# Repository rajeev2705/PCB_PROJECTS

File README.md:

# PCB_PROJECTS
Welcome to my PCB projects repository! This space is dedicated to documenting my journey in designing, creating, and improving printed circuit boards (PCBs). Here, I share various PCB projects, including schematics, layouts, bill of materials (BOM), and relevant documentation.

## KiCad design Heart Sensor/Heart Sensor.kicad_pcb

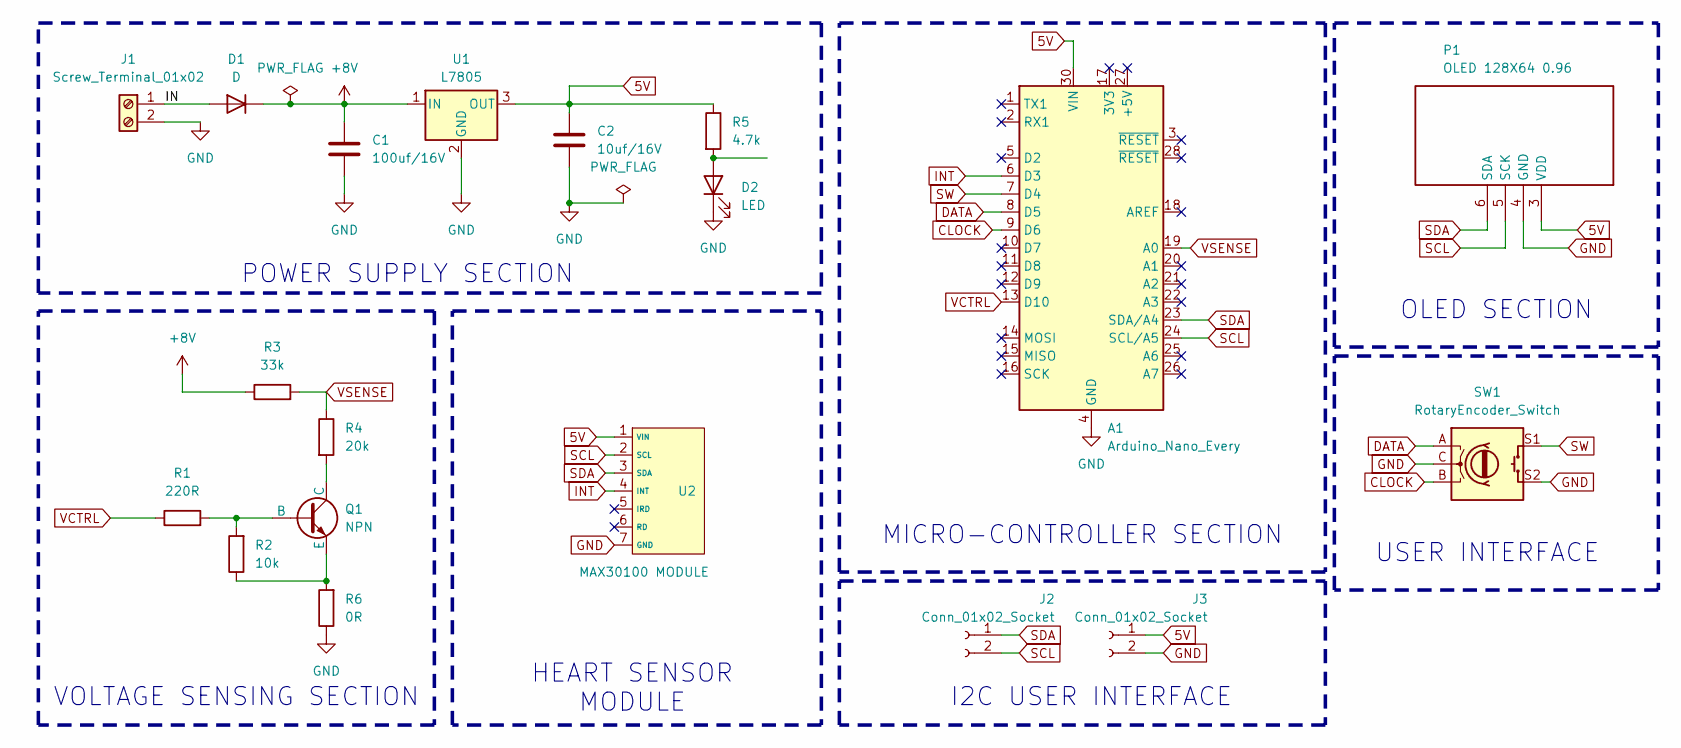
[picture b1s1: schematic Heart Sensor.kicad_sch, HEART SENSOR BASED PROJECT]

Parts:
A1: Arduino_Nano_Every; Arduino_Nano
C1: 100uf/16V; C_Radial_D5.0mm_H5.0mm_P2.00mm
C2: 10uf/16V; C_Radial_D5.0mm_H5.0mm_P2.00mm
D1: D; D_A-405_P7.62mm_Horizontal
D2: LED; LED_D3.0mm
J1: Screw_Terminal_01x02; TerminalBlock_4Ucon_1x02_P3.50mm_Horizontal_user
J2, J3: Conn_01x02_Socket; PinSocket_1x02_P2.54mm_Vertical
P1: OLED 128X64 0.96; OLED_MODULE _FOOTPRINT
Q1: NPN; TO-92L_Inline
R1: 220R; R_Axial_DIN0207_L6.3mm_D2.5mm_P10.16mm_Horizontal
R2: 10k; R_Axial_DIN0207_L6.3mm_D2.5mm_P10.16mm_Horizontal
R3: 33k; R_Axial_DIN0207_L6.3mm_D2.5mm_P10.16mm_Horizontal
R4: 20k; R_Axial_DIN0207_L6.3mm_D2.5mm_P10.16mm_Horizontal
R5: 4.7k; R_Axial_DIN0207_L6.3mm_D2.5mm_P10.16mm_Horizontal
R6: 0R; R_Axial_DIN0207_L6.3mm_D2.5mm_P10.16mm_Horizontal
SW1: RotaryEncoder_Switch; rotary_ncodeer
U1: L7805; TO-220-3_Vertical
U2: MAX30100 MODULE; MAX30100_MODULE

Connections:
5V: A1.30 (VIN), C2.1, J3.1, P1.3 (VDD), R5.1, U1.3 (OUT), U2.1 (VIN)
+8V: C1.1, D1.1 (K), R3.1, U1.1 (IN)
/IN: D1.2 (A), J1.1
CLOCK: A1.9 (D6), SW1.B
DATA: A1.8 (D5), SW1.A
GND: A1.4 (GND), A1.29 (GND), C1.2, C2.2, D2.1 (K), J1.2, J3.2, P1.4 (GND), R6.1, SW1.C, SW1.S2, U1.2 (GND), U2.7 (GND)
INT: A1.6 (D3), U2.4 (INT)
unnamed: D2.2 (A), R5.2
unnamed: Q1.2 (B), R1.2, R2.2
unnamed: Q1.1 (C), R4.2
unnamed: Q1.3 (E), R2.1, R6.2
SCL: A1.24 (SCL/A5), J2.2, P1.5 (SCK), U2.2 (SCL)
SDA: A1.23 (SDA/A4), J2.1, P1.6 (SDA), U2.3 (SDA)
SW: A1.7 (D4), SW1.S1
VCTRL: A1.13 (D10), R1.1
VSENSE: A1.19 (A0), R3.2, R4.1

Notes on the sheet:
HEART SENSOR MODULE
USER INTERFACE
I2C USER INTERFACE
POWER SUPPLY SECTION
VOLTAGE SENSING SECTION
OLED SECTION
MICRO-CONTROLLER SECTION

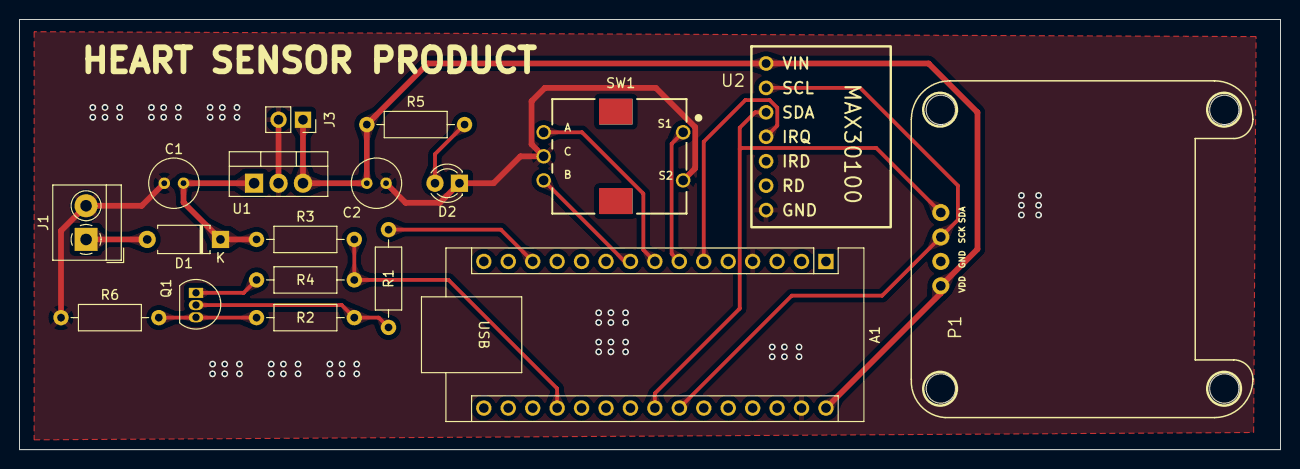
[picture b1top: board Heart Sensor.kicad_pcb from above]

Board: 2 copper layers, 131.1 x 44.7 mm, 18 parts (0 on the bottom side), 16 nets.

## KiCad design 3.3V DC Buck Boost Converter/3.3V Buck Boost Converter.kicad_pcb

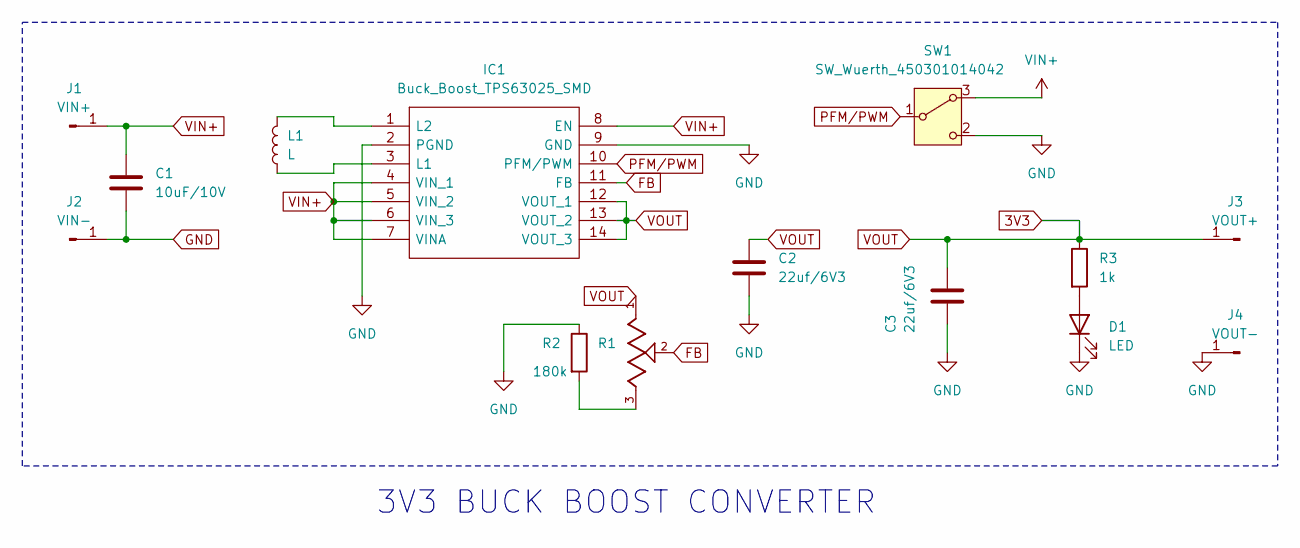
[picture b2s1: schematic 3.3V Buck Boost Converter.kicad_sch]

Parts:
C1: 10uF/10V; C_Radial_D6.3mm_H11.0mm_P2.50mm
C2, C3: 22uf/6V3; C_Radial_D6.3mm_H11.0mm_P2.50mm
D1: LED; LED_D3.0mm
IC1: Buck_Boost_TPS63025_SMD; IC_BuckBoost_TPS630250RNCT_VQFN14_2x3mm; Manufacturer_Part_Number TPS630250RNCT; Mouser Part Number 595-TPS630250RNCT
J1: VIN+; TestPoint_Pad_1.0x1.0mm
J2: VIN-; TestPoint_Pad_1.0x1.0mm
J3: VOUT+; TestPoint_Pad_1.0x1.0mm
J4: VOUT-; TestPoint_Pad_1.0x1.0mm
L1: L; XFL7015102MEB
R1: PT01-D120K1-B103; TrimPot_10k_SMD; PARTREV 1.0; DigiKey_Part_Number 2223-PT01-D120K1-B103-ND
R2: 180k; R_Axial_DIN0207_L6.3mm_D2.5mm_P10.16mm_Horizontal
R3: 1k; R_Axial_DIN0207_L6.3mm_D2.5mm_P10.16mm_Horizontal
SW1: SW_Wuerth_450301014042; SW_Slide-03_Wuerth-WS-SLTV_10x2.5x6.4_P2.54mm

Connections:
3V3: C2.1, C3.1, IC1.12 (VOUT_1), IC1.13 (VOUT_2), IC1.14 (VOUT_3), J3.1, R1.1, R3.1
FB: IC1.11 (FB), R1.2
GND: C1.2, C2.2, C3.2, D1.1 (K), IC1.2 (PGND), IC1.9 (GND), J2.1, J4.1, R2.1, SW1.2 (C)
unnamed: D1.2 (A), R3.2
unnamed: IC1.3 (L1), L1.1
unnamed: IC1.1 (L2), L1.2
unnamed: R1.3, R2.2
PFM/PWM: IC1.10 (PFM/PWM), SW1.1 (B)
VIN+: C1.1, IC1.4 (VIN_1), IC1.5 (VIN_2), IC1.6 (VIN_3), IC1.7 (VINA), IC1.8 (EN), J1.1, SW1.3 (A)

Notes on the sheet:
3V3 BUCK BOOST CONVERTER

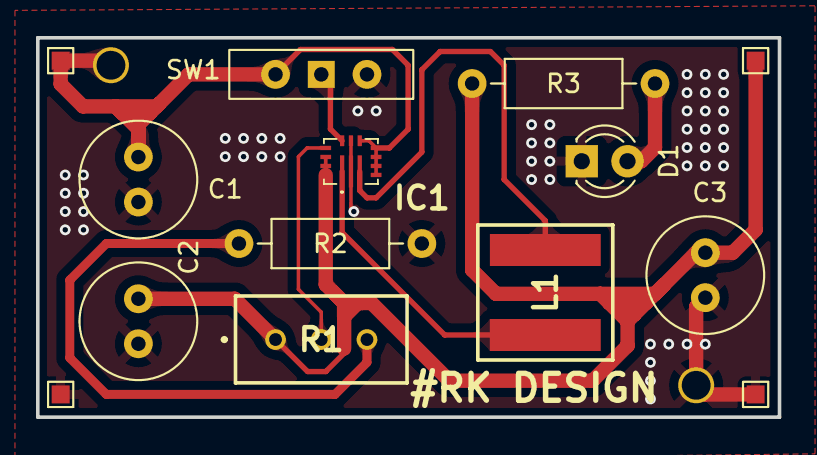
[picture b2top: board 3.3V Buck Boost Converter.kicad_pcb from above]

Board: 2 copper layers, 41.2 x 21.1 mm, 14 parts (0 on the bottom side), 9 nets.

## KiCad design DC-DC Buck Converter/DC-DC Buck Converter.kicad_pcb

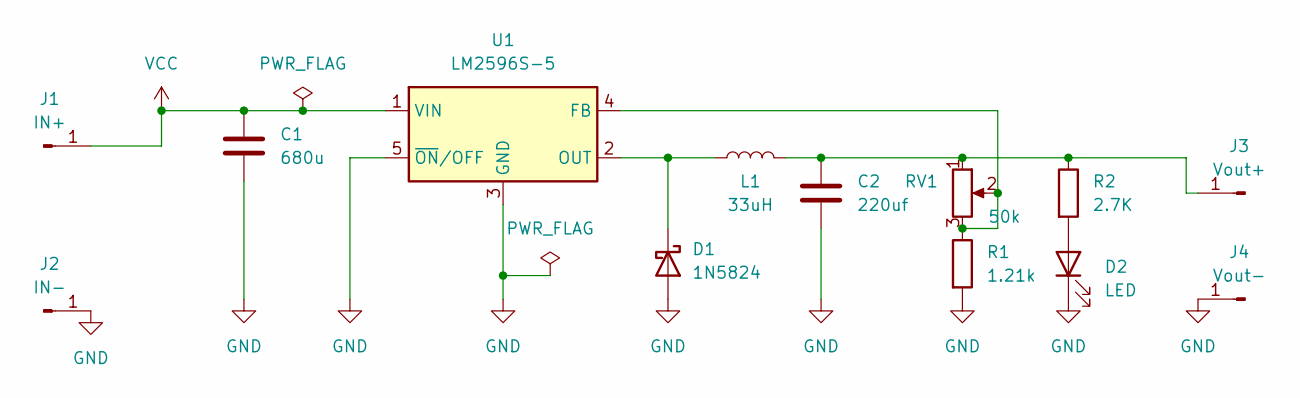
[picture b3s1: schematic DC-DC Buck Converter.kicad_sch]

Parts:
C1: 680u; CAP-SMD_BD6.3-L6.6-W6.6-FD
C2: 220uf; CAP-SMD_BD6.3-L6.6-W6.6-FD
D1: 1N5824; SCHOTTKYDIODE_SMD
D2: LED; LED_0603_1608Metric_Pad1.05x0.95mm_HandSolder
J1: IN+; SolderWire-0.1sqmm_1x01_D0.4mm_OD1mm
J2: IN-; SolderWire-0.1sqmm_1x01_D0.4mm_OD1mm
J3: Vout+; SolderWire-0.1sqmm_1x01_D0.4mm_OD1mm
J4: Vout-; SolderWire-0.1sqmm_1x01_D0.4mm_OD1mm
L1: 33uH; IND_SRP6540-1R0M
R1: 1.21k; R_0603_1608Metric_Pad0.98x0.95mm_HandSolder
R2: 2.7K; R_0603_1608Metric_Pad0.98x0.95mm_HandSolder
RV1: 50k; TrimPot_10k_SMD
U1: LM2596S-5; TO-263-5_TabPin3

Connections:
GND: C1.2, C2.2, D1.2 (A), D2.1 (K), J2.1, J4.1, R1.2, U1.3 (GND), U1.5 (~ON/OFF)
unnamed: D1.1 (K), L1.1, U1.2 (OUT)
unnamed: D2.2 (A), R2.2
unnamed: C2.1, J3.1, L1.2, R2.1, RV1.1
unnamed: R1.1, RV1.2, RV1.3, U1.4 (FB)
VCC: C1.1, J1.1, U1.1 (VIN)

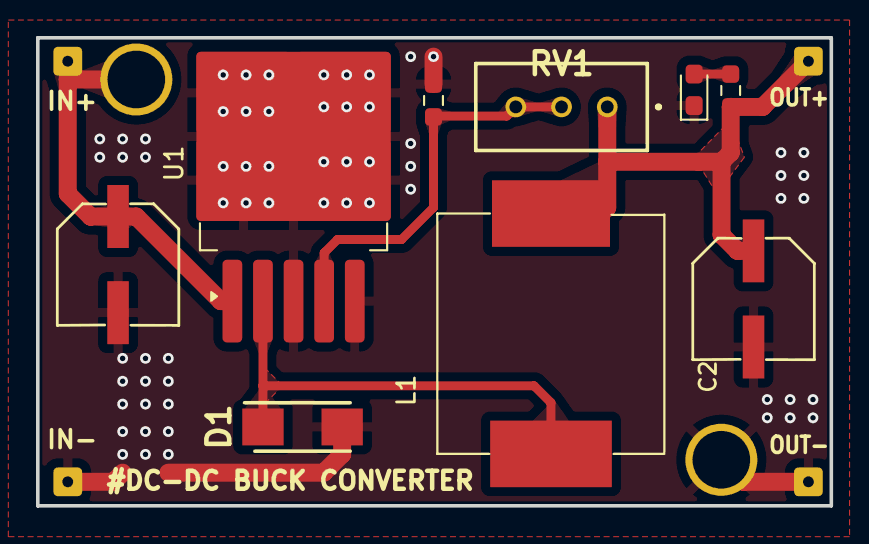
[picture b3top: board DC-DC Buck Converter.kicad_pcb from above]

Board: 2 copper layers, 44.1 x 26.0 mm, 13 parts (0 on the bottom side), 6 nets.

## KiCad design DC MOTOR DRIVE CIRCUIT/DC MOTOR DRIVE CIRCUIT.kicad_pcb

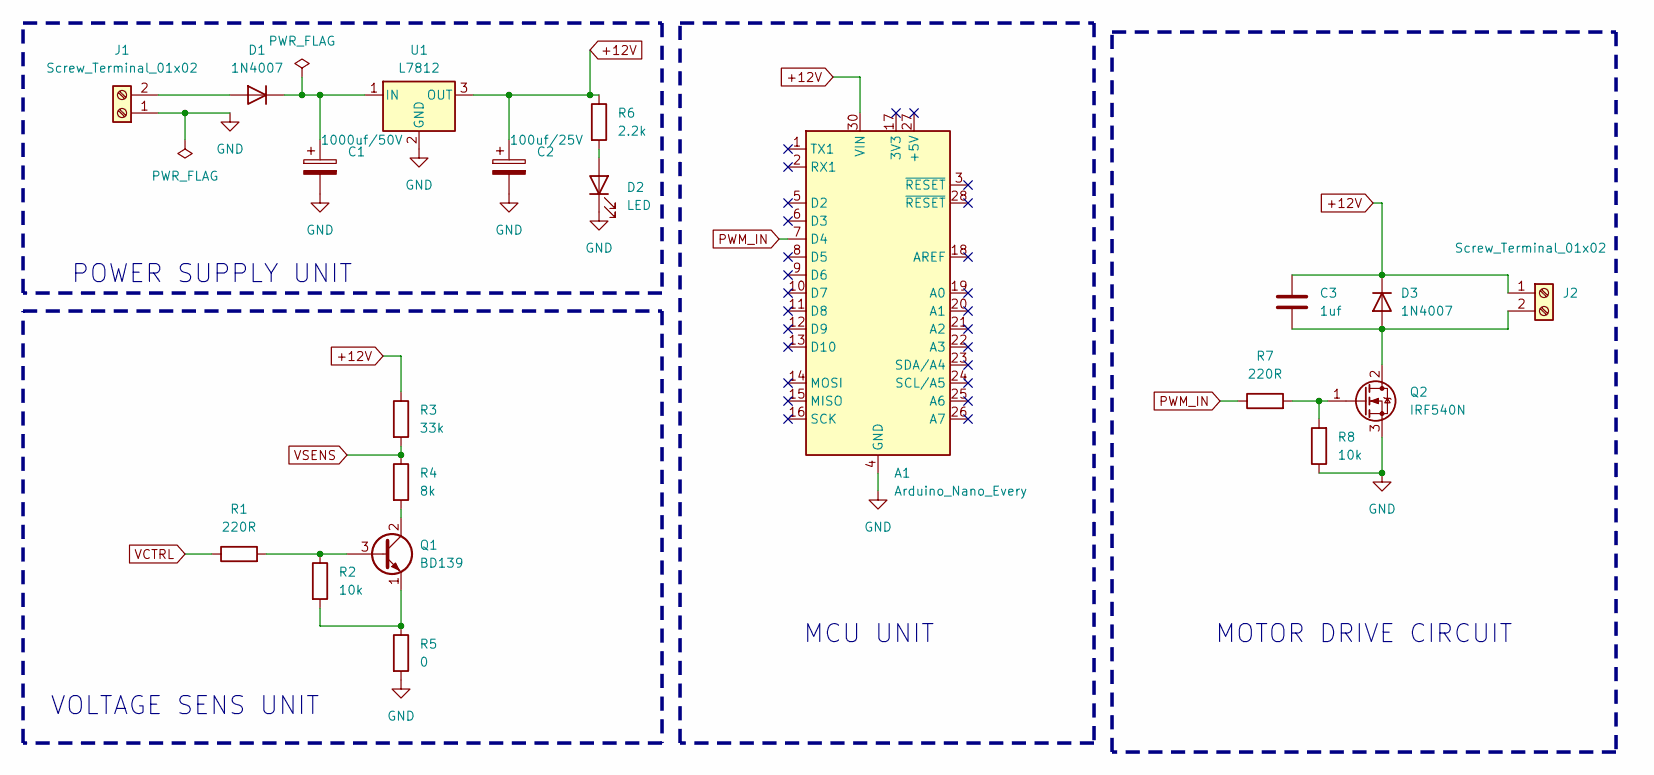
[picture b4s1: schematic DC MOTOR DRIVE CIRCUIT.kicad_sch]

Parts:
A1: Arduino_Nano_Every; Arduino_Nano
C1: 1000uf/50V; CP_Radial_D8.0mm_P3.50mm
C2: 100uf/25V; CP_Radial_D8.0mm_P3.50mm
C3: 1uf; C_Disc_D3.0mm_W1.6mm_P2.50mm
D1, D3: 1N4007; D_DO-41_SOD81_P10.16mm_Horizontal
D2: LED; LED_D3.0mm
J1, J2: Screw_Terminal_01x02; TerminalBlock_4Ucon_1x02_P3.50mm_Horizontal
Q1: BD139; TO-126-3_Vertical
Q2: IRF540N; TO-220-3_Vertical
R1, R7: 220R; R_Axial_DIN0204_L3.6mm_D1.6mm_P7.62mm_Horizontal
R2, R8: 10k; R_Axial_DIN0204_L3.6mm_D1.6mm_P7.62mm_Horizontal
R3: 33k; R_Axial_DIN0204_L3.6mm_D1.6mm_P7.62mm_Horizontal
R4: 8k; R_Axial_DIN0204_L3.6mm_D1.6mm_P7.62mm_Horizontal
R5: 0; R_Axial_DIN0204_L3.6mm_D1.6mm_P7.62mm_Horizontal
R6: 2.2k; R_Axial_DIN0204_L3.6mm_D1.6mm_P7.62mm_Horizontal
U1: L7812; TO-252-2

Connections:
+12V: A1.30 (VIN), C2.1, C3.1, D3.1 (K), J2.1, R3.1, R6.1, U1.3 (OUT)
GND: A1.4 (GND), A1.29 (GND), C1.2, C2.2, D2.1 (K), J1.1, Q2.3 (S), R5.2, R8.1, U1.2 (GND)
unnamed: D1.2 (A), J1.2
unnamed: C1.1, D1.1 (K), U1.1 (IN)
unnamed: D2.2 (A), R6.2
unnamed: C3.2, D3.2 (A), J2.2, Q2.2 (D)
unnamed: Q1.3 (B), R1.2, R2.1
unnamed: Q1.2 (C), R4.2
unnamed: Q1.1 (E), R2.2, R5.1
unnamed: Q2.1 (G), R7.2, R8.2
PWM_IN: A1.7 (D4), R7.1
VCTRL: R1.1
VSENS: R3.2, R4.1

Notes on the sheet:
MOTOR DRIVE CIRCUIT
VOLTAGE SENS UNIT
MCU UNIT
POWER SUPPLY UNIT

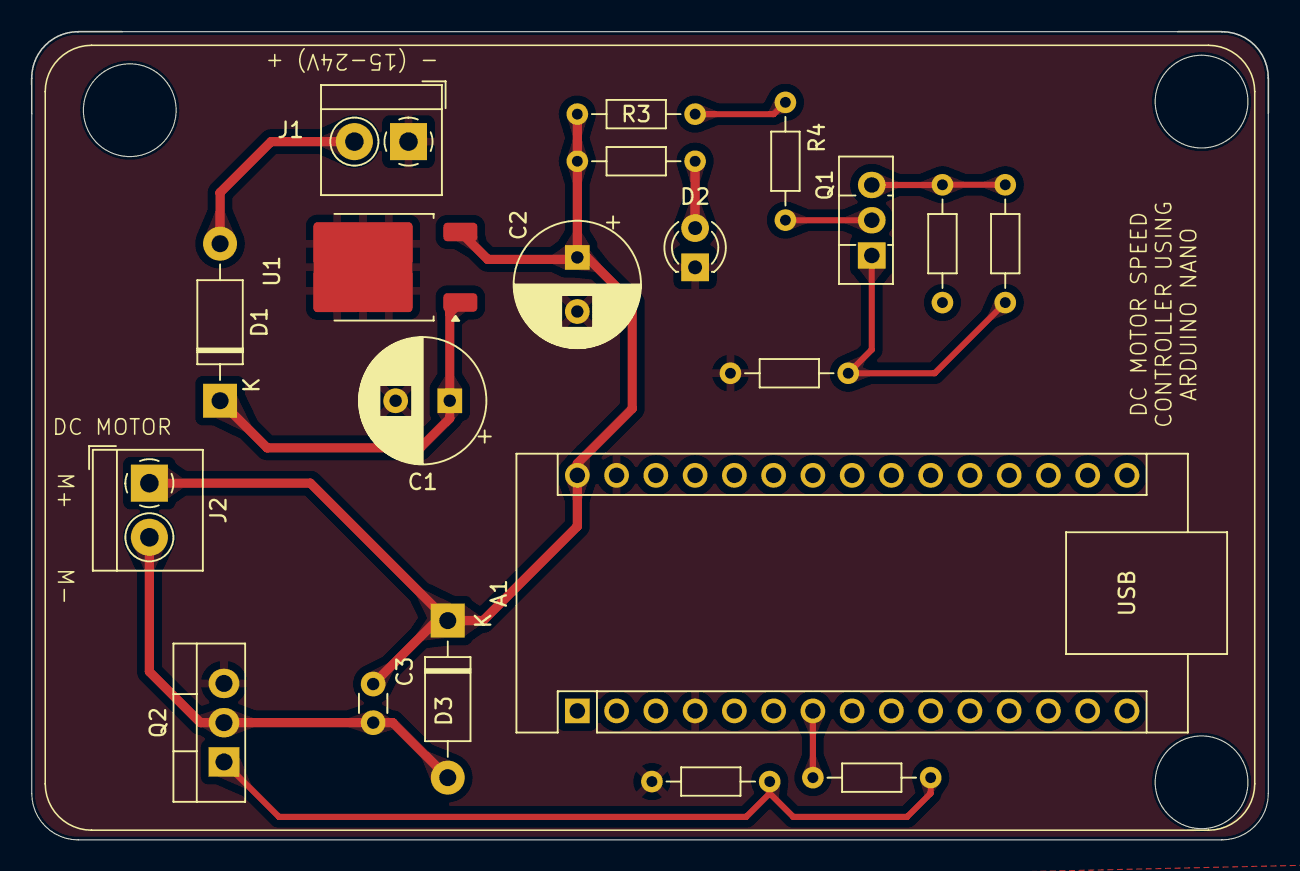
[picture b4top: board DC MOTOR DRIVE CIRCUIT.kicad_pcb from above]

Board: 2 copper layers, 80.0 x 52.3 mm, 20 parts (0 on the bottom side), 12 nets.

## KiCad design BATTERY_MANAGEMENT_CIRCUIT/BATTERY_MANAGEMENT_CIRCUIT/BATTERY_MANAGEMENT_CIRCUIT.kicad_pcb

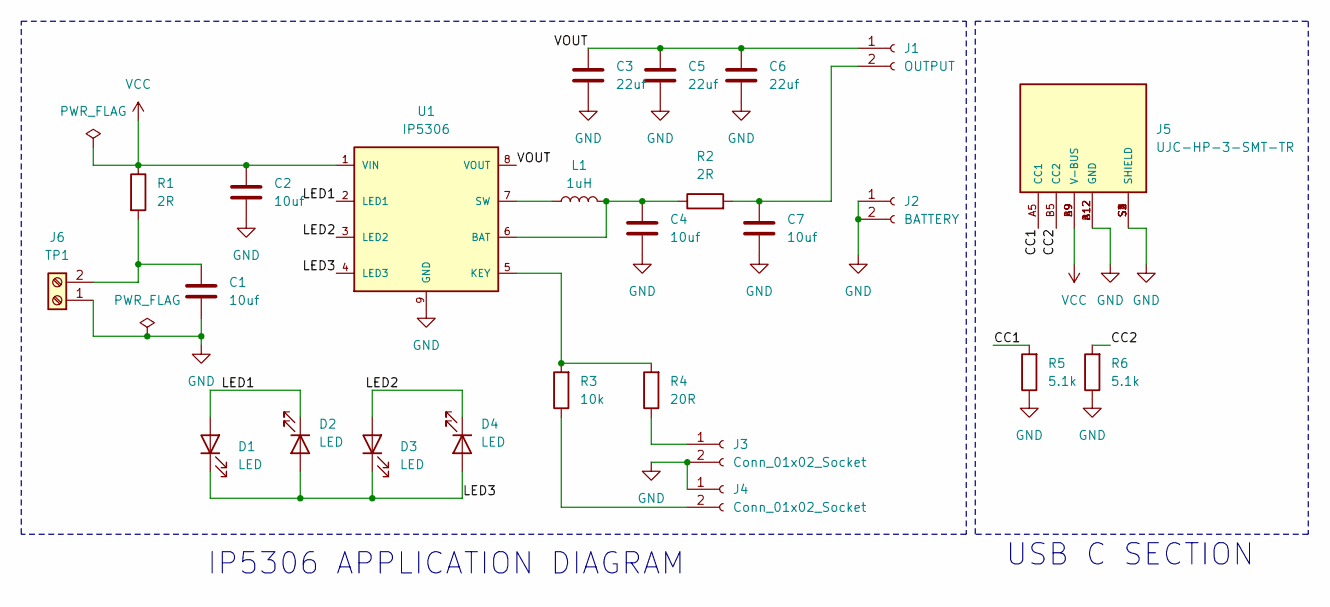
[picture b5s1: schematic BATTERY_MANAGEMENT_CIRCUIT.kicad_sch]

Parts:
C1, C2, C4, C7: 10uf; C_Disc_D3.0mm_W2.0mm_P2.50mm
C3, C5, C6: 22uf; C_Disc_D4.3mm_W1.9mm_P5.00mm
D1, D2, D3, D4: LED; LED_D3.0mm
J1: OUTPUT; PinHeader_1x02_P2.54mm_Vertical
J2: BATTERY; PinHeader_1x02_P2.54mm_Vertical
J3, J4: Conn_01x02_Socket; PinHeader_1x02_P2.54mm_Vertical
J5: UJC-HP-3-SMT-TR; CUI_UJC-HP-3-SMT-TR; PARTREV 04/30/2020
J6: TP1; TestPoint_2Pads_Pitch2.54mm_Drill0.8mm
L1: 1uH; IND_SRP6540-1R0M
R1, R2: 2R; R_Axial_DIN0204_L3.6mm_D1.6mm_P5.08mm_Horizontal
R3: 10k; R_Axial_DIN0204_L3.6mm_D1.6mm_P5.08mm_Horizontal
R4: 20R; R_Axial_DIN0204_L3.6mm_D1.6mm_P5.08mm_Horizontal
R5, R6: 5.1k; R_Axial_DIN0204_L3.6mm_D1.6mm_P5.08mm_Horizontal
U1: IP5306; SOIC127P600X165-9N

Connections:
/CC1: J5.A5 (CC1), R5.2
/CC2: J5.B5 (CC2), R6.2
/LED1: D1.2 (A), D2.1 (K), U1.2 (LED1)
/LED2: D3.2 (A), D4.1 (K), U1.3 (LED2)
/LED3: D1.1 (K), D2.2 (A), D3.1 (K), D4.2 (A), U1.4 (LED3)
/VOUT: C3.1, C5.1, C6.1, J1.1, U1.8 (VOUT)
GND: C1.2, C2.2, C3.2, C4.2, C5.2, C6.2, C7.2, J2.1, J2.2, J3.2, J4.1, J5.A12 (GND), J5.B12 (GND), J5.S1 (SHIELD), J5.S2 (SHIELD), J5.S3 (SHIELD), J5.S4 (SHIELD), J6.1, R5.1, R6.1, U1.9 (GND)
unnamed: C7.1, J1.2, R2.2
unnamed: J3.1, R4.1
unnamed: J4.2, R3.1
unnamed: C1.1, J6.2, R1.2
unnamed: C4.1, L1.2, R2.1, U1.6 (BAT)
unnamed: R3.2, R4.2, U1.5 (KEY)
unnamed: L1.1, U1.7 (SW)
VCC: C2.1, J5.A9 (V-BUS), J5.B9 (V-BUS), R1.1, U1.1 (VIN)

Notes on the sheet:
USB C SECTION
IP5306 APPLICATION DIAGRAM

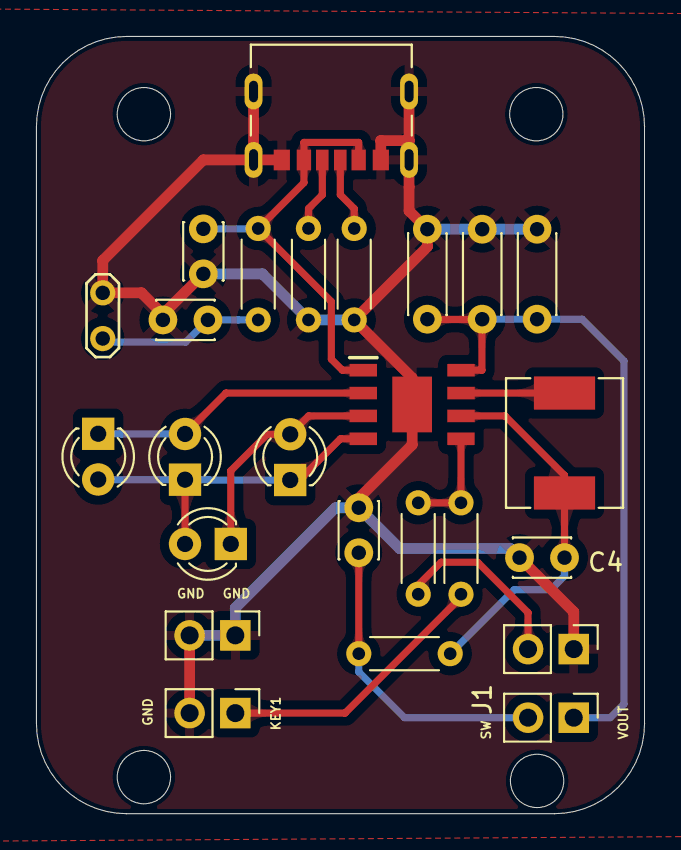
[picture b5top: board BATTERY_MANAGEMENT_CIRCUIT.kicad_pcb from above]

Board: 2 copper layers, 33.8 x 43.2 mm, 25 parts (0 on the bottom side), 15 nets.

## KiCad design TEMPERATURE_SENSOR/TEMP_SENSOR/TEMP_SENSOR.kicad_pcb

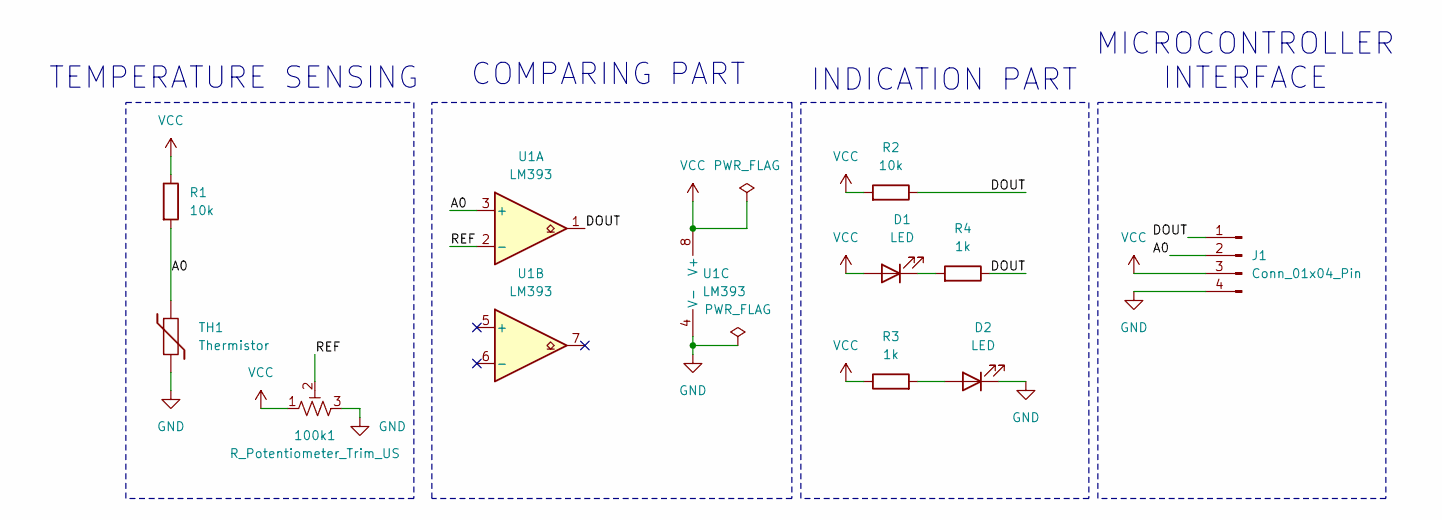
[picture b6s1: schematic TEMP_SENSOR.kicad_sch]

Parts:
100k1: R_Potentiometer_Trim_US; TRIM_3352T-1-504LF
D1, D2: LED; LED_0603_1608Metric
J1: Conn_01x04_Pin; PinHeader_1x04_P2.54mm_Horizontal
R1, R2: 10k; R_0603_1608Metric
R3, R4: 1k; R_0603_1608Metric
TH1: Thermistor; R_0805_2012Metric
U1: LM393; SOP-8_5.28x5.23mm_P1.27mm

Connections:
/A0: J1.2, R1.2, TH1.1, U1.3 (+); also elsewhere on the board
/DOUT: J1.1, R2.1, R4.1, U1.1
/REF: 100k1.2, U1.2 (-)
GND: 100k1.3, D2.1 (K), J1.4, TH1.2, U1.4 (V-); also elsewhere on the board
unnamed: D1.1 (K), R4.2
unnamed: D2.2 (A), R3.2
VCC: 100k1.1, D1.2 (A), J1.3, R1.1, R2.2, R3.1, U1.8 (V+)

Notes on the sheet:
MICROCONTROLLER INTERFACE
INDICATION PART
COMPARING PART
TEMPERATURE SENSING

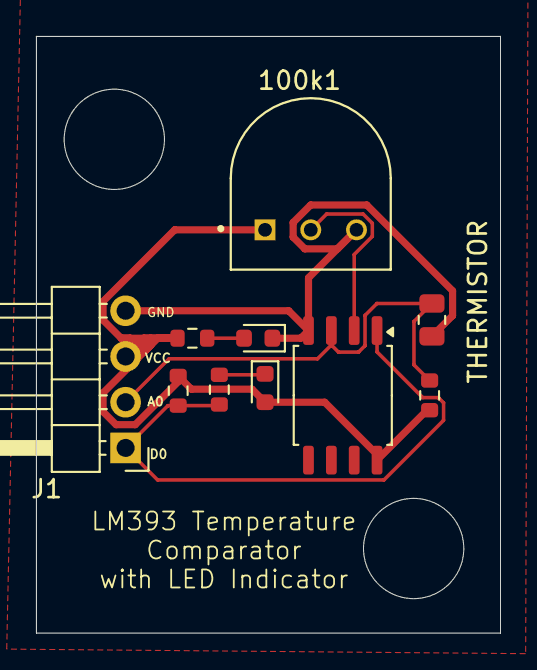
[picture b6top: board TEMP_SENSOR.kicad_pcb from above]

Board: 2 copper layers, 25.8 x 33.1 mm, 10 parts (0 on the bottom side), 7 nets.

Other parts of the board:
THERMISTOR: Thermistor; R_0805_2012Metric

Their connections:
/A0: THERMISTOR.1; also elsewhere on the board
GND: THERMISTOR.2; also elsewhere on the board

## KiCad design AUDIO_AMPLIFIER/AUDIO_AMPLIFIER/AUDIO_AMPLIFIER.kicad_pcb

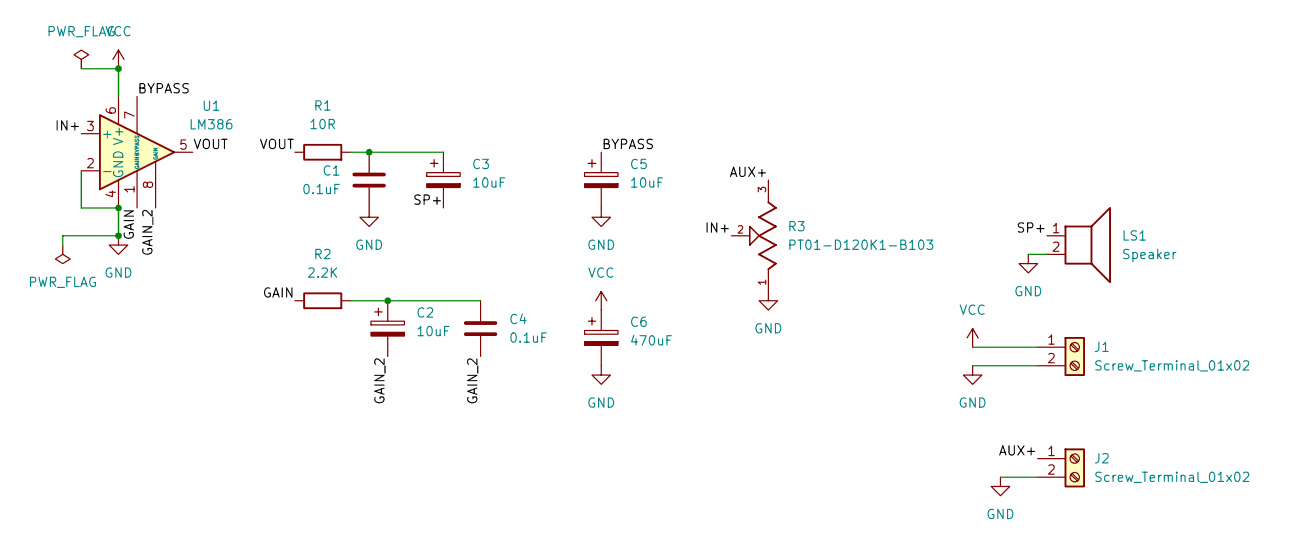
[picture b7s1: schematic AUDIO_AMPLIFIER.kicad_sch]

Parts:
C1, C4: 0.1uF; C_Disc_D5.0mm_W2.5mm_P2.50mm
C2, C3, C5: 10uF; CP_Radial_D5.0mm_P2.50mm
C6: 470uF; CP_Radial_D5.0mm_P2.50mm
J1, J2: Screw_Terminal_01x02; TerminalBlock_4Ucon_1x02_P3.50mm_Horizontal
LS1: Speaker; Altech_AK100_1x02_P5.00mm
R1: 10R; R_Axial_DIN0207_L6.3mm_D2.5mm_P5.08mm_Vertical
R2: 2.2K; R_Axial_DIN0207_L6.3mm_D2.5mm_P5.08mm_Vertical
R3: PT01-D120K1-B103; Potentiometer_Alps_RK163_Single_Horizontal; PARTREV 1.0; DigiKey_Part_Number 2223-PT01-D120K1-B103-ND
U1: LM386; SOIC-8_3.9x4.9mm_P1.27mm

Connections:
/AUX+: J2.1, R3.3
/BYPASS: C5.1, U1.7 (BYPASS)
/GAIN: R2.1, U1.1 (GAIN)
/GAIN_2: C2.2, C4.2, U1.8 (GAIN)
/IN+: R3.2, U1.3 (+)
/SP+: C3.2, LS1.1
/VOUT: R1.1, U1.5
GND: C1.2, C5.2, C6.2, J1.2, J2.2, LS1.2, R3.1, U1.2 (-), U1.4 (GND)
unnamed: C1.1, C3.1, R1.2
unnamed: C2.1, C4.1, R2.2
VCC: C6.1, J1.1, U1.6 (V+)

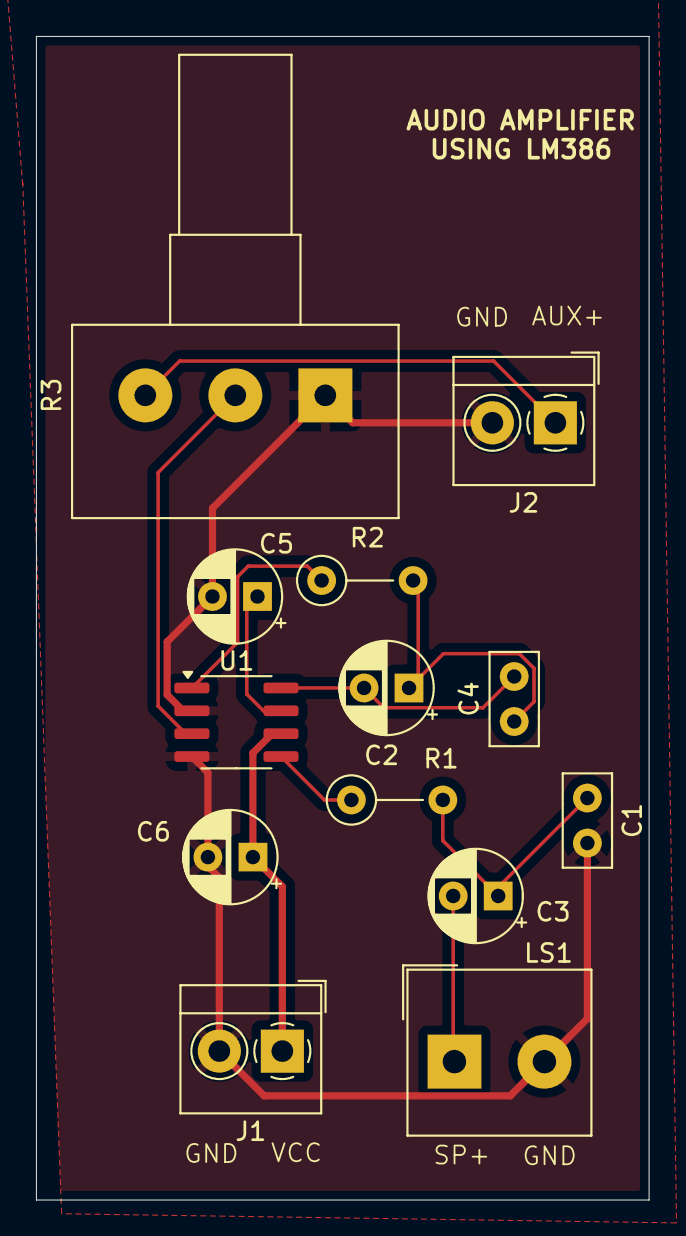
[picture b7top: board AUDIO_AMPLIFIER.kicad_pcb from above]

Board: 2 copper layers, 34.0 x 64.6 mm, 13 parts (0 on the bottom side), 11 nets.

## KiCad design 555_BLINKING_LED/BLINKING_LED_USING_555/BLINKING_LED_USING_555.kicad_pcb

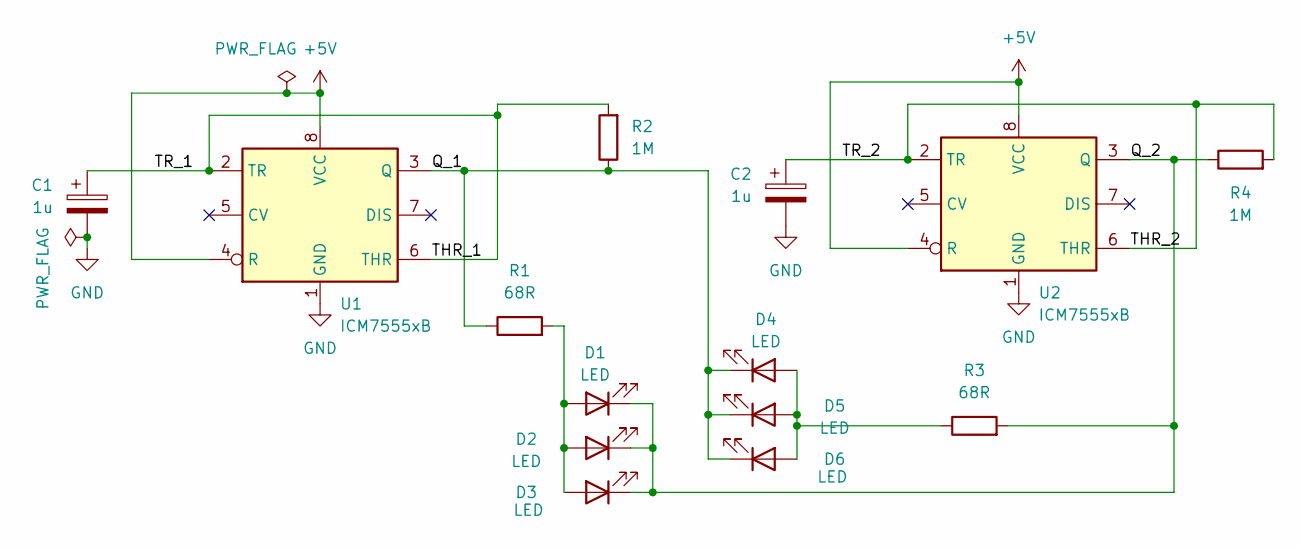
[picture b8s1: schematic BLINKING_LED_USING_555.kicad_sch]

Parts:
C1, C2: 1u; CP_Radial_D4.0mm_P1.50mm
D1, D2, D3, D4, D5, D6: LED; LED_D3.0mm
R1: 68R; R_Axial_DIN0207_L6.3mm_D2.5mm_P7.62mm_Horizontal
R2, R4: 1M; R_Axial_DIN0207_L6.3mm_D2.5mm_P10.16mm_Horizontal
R3: 68R; R_Axial_DIN0207_L6.3mm_D2.5mm_P10.16mm_Horizontal
U1: ICM7555xB; SOIC-8-N7_3.9x4.9mm_P1.27mm
U2: ICM7555xB; SOIC-8_3.9x4.9mm_P1.27mm

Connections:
+5V: U1.4 (R), U1.8 (VCC), U2.4 (R), U2.8 (VCC)
/Q_1: D4.1 (K), D5.1 (K), D6.1 (K), R1.1, R2.1, U1.3 (Q)
/Q_2: D1.1 (K), D2.1 (K), D3.1 (K), R3.2, R4.1, U2.3 (Q)
/THR_1: C1.1, R2.2, U1.2 (TR), U1.6 (THR)
/THR_2: C2.1, R4.2, U2.2 (TR), U2.6 (THR)
GND: C1.2, C2.2, U1.1 (GND), U2.1 (GND)
unnamed: D1.2 (A), D2.2 (A), D3.2 (A), R1.2
unnamed: D4.2 (A), D5.2 (A), D6.2 (A), R3.1

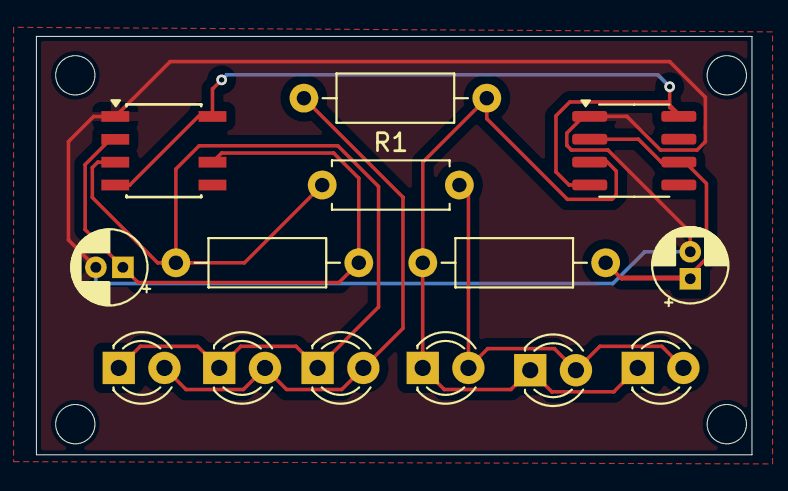
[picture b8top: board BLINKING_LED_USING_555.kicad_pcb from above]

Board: 2 copper layers, 39.8 x 23.2 mm, 14 parts (0 on the bottom side), 8 nets.

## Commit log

2024-06-22 PCB Project Uploaded
2024-06-22 .gitignore file added
2024-06-22 replaced kicad_prl
2024-06-22 deleted kicad_prl
2024-06-24 pcb updated with accrate component names
2024-06-24 File_Shifted
2024-06-24 New_KIcad FIle added
2024-06-24 Modified
2024-06-25 not good
2024-06-25 pcb and schematic updated
2024-06-26 only saved
2024-06-26 error
2024-06-26 Perfect PCB
2024-06-28 Create ESP32_OPEN_SRC_PROJECT_DIY
    I'm creating a DIY project of ESP32 microcontroller. It's open-source because I want to explore how it's built and organized.
2024-06-28 only saved changes
2024-06-28 perfect
2024-06-29 ac load switch added
2024-06-29 everything deleted
2024-06-29 re-copied all
2024-06-29 minor changes
2024-07-02 finalised
2024-07-02 3d image pcb with case
2024-07-02 .ignore added
2024-07-03 deleted empty files
2024-07-16 header pin added
2024-08-01 arduino created
2024-08-02 555 with leds police light flasher
2024-08-02 temp sensor initialized and notes added in 555
2024-08-02 temp sensor project made
2024-08-03 temp sensor module refined and audio amplifier made
2024-08-03 BMS made
2024-08-03 Create Description
2024-08-03 Rename Description to Description.md
2024-08-15 changes and added BMC
2024-08-29 Esp32,Sdcard initialized,heart sensor project completed--Project
2024-08-29 heart sensor --BOM added
2024-08-29 heart sensor --pcb file pdf
2024-08-30 dc motor speed control pcb
2024-09-03 DC-DC Buck COnverter MOdule made
2024-09-06 refined
2024-11-16 New Project Initialized(Example)
2025-07-23 dont know updates
